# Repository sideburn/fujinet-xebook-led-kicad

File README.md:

# FN32ROV XEBook LED Board

A small daughter board carrying the three FujiNet status LEDs (WiFi, Bluetooth, SIO) for
the [FN32ROV-XEBook-KiCad](../FN32ROV-XEBook-KiCad) main board, which mounts the FujiNet
FN32ROV WiFi/SIO adapter permanently inside an XEBook laptop build.

On the main board, the LEDs and buttons were moved off-PCB onto JST pigtails so they can
be panel-mounted separately (see that project's `CLAUDE.md`, "External LED board
interface (J_LED1)"). This board is that panel-mounted LED daughter board.

## What's on it

- D1 (WiFi), D2 (Bluetooth), D3 (SIO) — 0402 SMD LEDs, common-anode to 3V3, each cathode
  wired back to its own signal pin. The ESP32 on the main board sinks current by driving
  the corresponding GPIO low.
  - D1 is **green** (Rohm SML-P12PTT86R) — the original FN32ROV-1.7.1 WiFi LED was white
    (SunLED XZBWR68F5MAV-3, still available); green is a deliberate choice for this build,
    not a substitution forced by availability. The main board's
    R13 was resized from 1k to 2.7k to keep the current sane for the green LED's lower
    forward voltage (~2.2V vs ~2.9V for white).
  - D2 (blue, OSRAM LB QH9G-N1OO-35-1) and D3 (orange, Rohm SML-P12DTT86R) are unchanged
    from the original FN32ROV-1.7.1 BOM.
- J1 — 4-pin JST PH vertical header, **through-hole**
  (`JST_PH_B4B-PH-K_1x04_P2.00mm_Vertical`), mounted on the **back** of the board and
  hand-soldered. An earlier revision used an SMD connector specifically to avoid THT
  pads plating through to the light-pipe side, but assembling both sides of the board
  turned out to be too costly for JLCPCB assembly — hand-soldering a THT part is cheaper.
  Since a THT part's copper unavoidably lands on both faces, J1 is instead offset well
  clear of the LED row in Y (the board's height was grown from 10mm to 14mm specifically
  to make room for this), so its pads don't land under a light pipe. Mates via a JST PH
  pigtail to J_LED1 on the main board, pin-for-pin (1=3V3, 2=LED_WIFI, 3=LED_BT,
  4=LED_SIO).

Current-limiting resistors are **not** on this board — they live on the main board
(R13/R14/R15) since this board only ever sees the LED forward voltage drop.

## Mechanical

- Board outline: 40mm x 14mm.
- LEDs sit on 10mm pitch, centered on the board (x = 10/20/30mm from the left edge,
  y = 3mm), aligned to the XEBook case's light-pipe positions. LEDs use SMD packages
  with panel light pipes carrying light out to the case surface — no hole is drilled in
  the PCB itself under each LED.
- Two M2 clearance holes (`MountingHole_2.2mm_M2`), 4mm in from each end, at y = 7mm
  (the board's vertical center) — 4mm below the LED row.
- J1's housing sits with its near edge at that same y = 7mm row (pad row at y = 9.2mm,
  2.2mm further down — that offset is baked into the connector's footprint). This gives
  the light-pipe housing (~2.1mm radius around each LED) about 1.9mm of clearance to
  J1's physical housing edge — the dimension that actually matters here, not the copper
  pad edges, since it's the plastic housings that would physically collide if this were
  too tight.
- Board thickness: 1.6mm (JLCPCB/industry standard, matches the main board).

## Status

Work in progress — schematic captured and footprints/nets placed on the PCB (ERC clean,
DRC clean, schematic/PCB parity clean). **Not yet routed** — the user routes copper by
hand in the KiCad GUI. Not yet fabricated.

## Tooling

Built with KiCad 9. `kicad-cli sch erc` / `kicad-cli pcb drc --schematic-parity` are used
to verify the design as it's built.

## License

[CERN Open Hardware Licence Version 2 - Strongly Reciprocal](LICENSE)
(CERN-OHL-S-2.0), matching the main board.

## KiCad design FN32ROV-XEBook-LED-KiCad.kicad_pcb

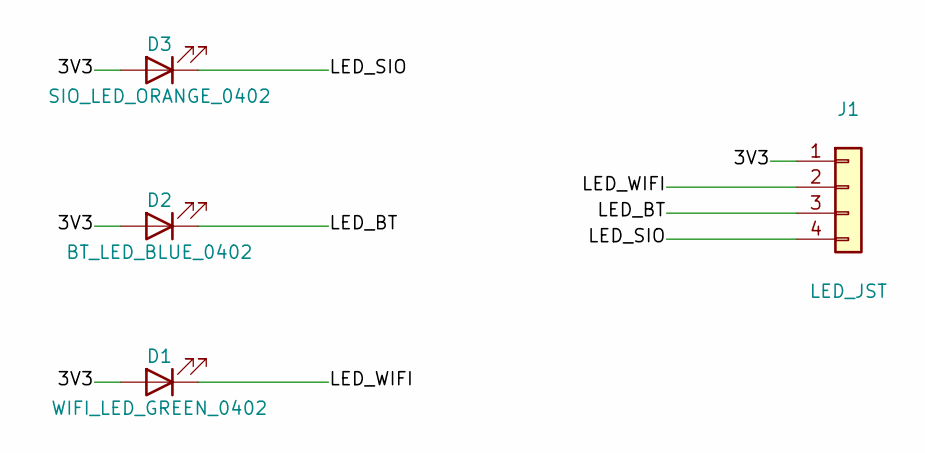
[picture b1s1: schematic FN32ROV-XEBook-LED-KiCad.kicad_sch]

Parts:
D1: WIFI_LED_GREEN_0402; LED_0402_1005Metric; LCSC C471422
D2: BT_LED_BLUE_0402; LED_0402_1005Metric; LCSC C30584803
D3: SIO_LED_ORANGE_0402; LED_0402_1005Metric; LCSC C28310436
J1: LED_JST; JST_PH_B4B-PH-K_1x04_P2.00mm_Vertical; LCSC C265289

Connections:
/3V3: D1.2 (A), D2.2 (A), D3.2 (A), J1.1
/LED_BT: D2.1 (K), J1.3
/LED_SIO: D3.1 (K), J1.4
/LED_WIFI: D1.1 (K), J1.2

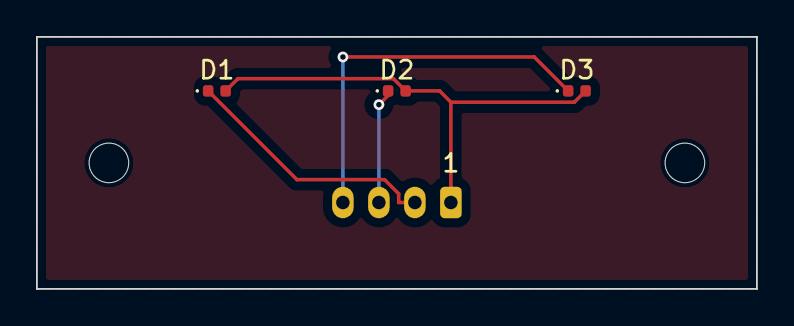
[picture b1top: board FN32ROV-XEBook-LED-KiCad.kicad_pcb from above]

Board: 2 copper layers, 40.0 x 14.0 mm, 6 parts (1 on the bottom side), 4 nets.

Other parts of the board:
MH1, MH2: MountingHole_2.2mm_M2

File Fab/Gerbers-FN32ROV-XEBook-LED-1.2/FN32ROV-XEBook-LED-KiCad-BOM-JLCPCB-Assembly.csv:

Reference,Value,Footprint,Qty,LCSC
D1,WIFI_LED_GREEN_0402,LED_SMD:LED_0402_1005Metric,1,C471422
D2,BT_LED_BLUE_0402,LED_SMD:LED_0402_1005Metric,1,C30584803
D3,SIO_LED_ORANGE_0402,LED_SMD:LED_0402_1005Metric,1,C28310436
